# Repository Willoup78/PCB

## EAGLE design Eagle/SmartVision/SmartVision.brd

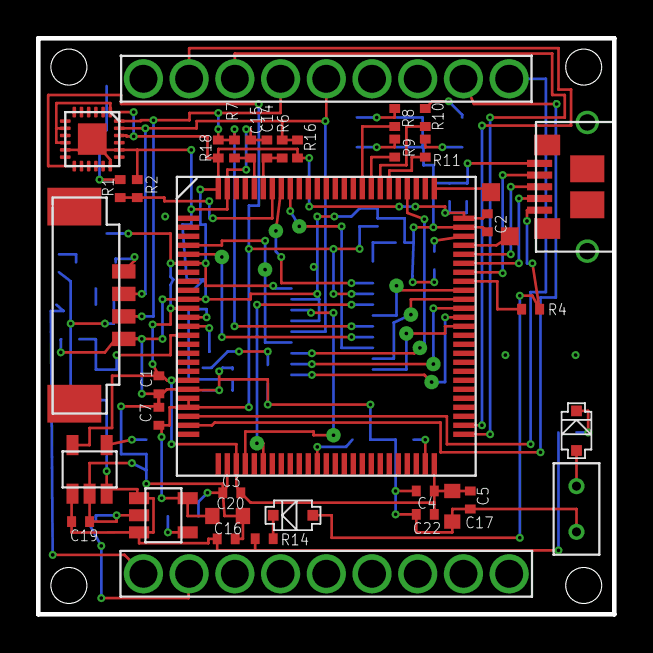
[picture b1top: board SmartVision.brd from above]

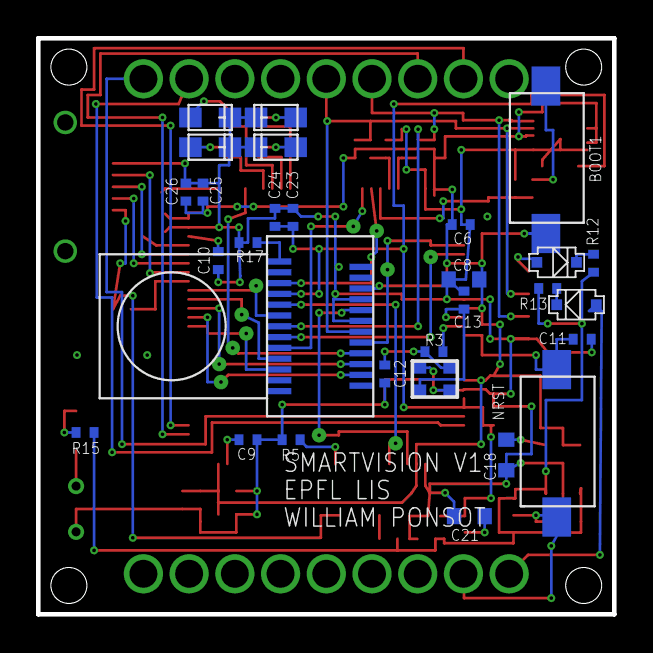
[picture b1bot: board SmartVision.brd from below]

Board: 2 copper layers, 32.0 x 32.0 mm, 66 parts (29 on the bottom side), 58 nets.

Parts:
C1, C2, C3, C4, C5, C6, C7, C11, C22, C23, C24, C25, C26: 100nF; SMALL_MAVRIC_SMALL_MAVRIC_CAPACITOR_C0402
C8: 10uF, 10V; SMALL_MAVRIC_SMALL_MAVRIC_CAPACITOR_C0603
C9, C10: 2.2uF; SMALL_MAVRIC_SMALL_MAVRIC_CAPACITOR_C0402
C12, C13: 12pF; SMALL_MAVRIC_SMALL_MAVRIC_CAPACITOR_C0402
C14, C15: 22pF; SMALL_MAVRIC_SMALL_MAVRIC_CAPACITOR_C0402
C16, C19: 1uF; SMALL_MAVRIC_SMALL_MAVRIC_CAPACITOR_C0402
C17, C18, C20, C21: 4.7uF; SMALL_MAVRIC_SMALL_MAVRIC_CAPACITOR_C0603
R1, R2, R5: 1K; SMALL_MAVRIC_SMALL_MAVRIC_RESISTOR_R0402
R3, R8, R9, R10, R11: 402; SMALL_MAVRIC_SMALL_MAVRIC_RESISTOR_R0402
R4, R6, R7, R16, R18: 4.7K; SMALL_MAVRIC_SMALL_MAVRIC_RESISTOR_R0402
R12, R13: 28; SMALL_MAVRIC_SMALL_MAVRIC_RESISTOR_R0402
R14, R15: 12.5; SMALL_MAVRIC_SMALL_MAVRIC_RESISTOR_R0402
R17: 10K; SMALL_MAVRIC_SMALL_MAVRIC_RESISTOR_R0402
U1: SMALL_MAVRIC_IMU_MPU-9250; SMALL_MAVRIC_SMALL_MAVRIC_QFN-24_3.0X3.0MM
U$1: STM32F407VGT6-100
U$2, U$7: VOLTAGE_REGULATOR_3V
U$4: MICRO_USB_PLUG
U$11: CON_CAMERA_FPC_25P_0.3MM
U$29, U$31: SWITCH_OFF_(ON)
U$40, U$41, U$42, U$43: LED
U$52: CON_2.54MM_18PINS_STACKABLE
U$53: CON_1.25MM_4PINS
U$54, U$55, U$57, U$61: DIODE_SCHOTTKY
U$59: CON_2.54MM_2PINS
U$63, U$64: PAD_FLASH
Y1: SMALL_MAVRIC_ABM10; SMALL_MAVRIC_OSCILLATOR_ABM10

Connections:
CAN2_RX: U$1.P51, U$52.P16
CAN2_TX: U$1.P52, U$52.P17
D0: U$1.P63, U$11.P23
D1: U$1.P64, U$11.P2
D2: U$1.P65, U$11.P3
D3: U$1.P66, U$11.P22
D4: U$1.P79, U$11.P4
D5: U$1.P92, U$11.P21
D6: U$1.P4, U$11.P5
D7: U$1.P5, U$11.P20
GND: C1.2, C2.2, C3.2, C4.2, C5.2, C6.2, C7.2, C8.2, C9.2, C10.2, C11.1, C12.2, C13.2, C14.2, C15.2, C16.2, C17.1, C18.2, C19.2, C20.1, C21.2, C22.2, C23.2, C24.2, C25.2, C26.2, R2.1, R5.2, R17.1, U1.11, U1.18, U1.20, U1.CENTRAL_PAD, U$1.P10, U$1.P20, U$1.P27, U$1.P74, U$1.P99, U$2.P2, U$4.P5, U$7.P2, U$11.P7, U$11.P9, U$29.P$1, U$40.C, U$41.C, U$42.C, U$43.C, U$52.P2, U$53.P4, U$59.P2, Y1.2, Y1.4
HSYNC: U$1.P29, U$11.P8
I2C_SCL: R6.2, R16.1, U1.23, U$11.P6, U$52.P14, U$53.P2
I2C_SDA: R7.2, R18.1, U1.24, U$11.P19, U$52.P15, U$53.P3
unnamed: C21.1, U$7.P4
unnamed: C18.1, U$2.P4
unnamed: R17.2, U$11.P13
unnamed: R11.2, U$1.P81
unnamed: R10.2, U$1.P82
unnamed: R9.2, U$1.P83
unnamed: R8.2, U$1.P84
unnamed: C13.1, U$1.P12, Y1.3
unnamed: R8.1, U$40.A
unnamed: C12.1, R3.2, Y1.1
unnamed: R9.1, U$41.A
unnamed: R10.1, U$42.A
unnamed: R3.1, U$1.P13
unnamed: C15.1, R7.1, U$1.P96
unnamed: C9.1, U$1.P49
unnamed: C10.1, U$1.P73
unnamed: C14.1, R6.1, U$1.P95
unnamed: R4.1, U$1.P68
unnamed: C11.2, U$1.P14, U$29.P$2
unnamed: R1.1, U$31.P$2
unnamed: R1.2, R2.2, U$1.P94
unnamed: R5.1, U$1.P37
unnamed: R11.1, U$43.A
unnamed: R13.1, U$61.P2
unnamed: R15.1, U$54.P2
unnamed: R12.1, U$55.P2
unnamed: R14.1, U$57.P2
PCLK: U$1.P31, U$11.P17
SWCLK: U$1.P76, U$63.P$1
SWDIO: U$1.P72, U$64.P$1
UART4_RX: U$1.P24, U$52.P11
UART4_TX: U$1.P23, U$52.P10
USB_D+: U$1.P71, U$4.P3
USB_D-: U$1.P70, U$4.P2
USB_ID: U$1.P69, U$4.P4
USB_VBUS: R4.2, U$4.P1, U$57.P1
VBAT: C16.1, C19.1, R12.2, R13.2, R14.2, R15.2, U$2.P1, U$2.P3, U$7.P1, U$7.P3
VBAT_C: U$53.P1, U$55.P1
VBAT_P: U$54.P1, U$59.P1
VBAT_S: U$52.P1, U$61.P1
VCC: C1.1, C2.1, C3.1, C4.1, C5.1, C6.1, C8.1, C17.2, C22.1, C25.1, C26.1, R16.2, R18.2, U1.1, U1.8, U1.10, U1.22, U$1.P6, U$1.P11, U$1.P19, U$1.P28, U$1.P50, U$1.P75, U$1.P100, U$2.P5, U$11.P10, U$31.P$1
VCC_ANA: C7.1, C20.2, C23.1, C24.1, U1.13, U$1.P21, U$1.P22, U$7.P5, U$11.P16
VSYNC: U$1.P93, U$11.P15
XCLK: U$1.P67, U$11.P18

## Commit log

2016-05-06 PCB schematics done !
2016-05-09 Fix supply and boot problem
2016-05-09 Routing mostly complete !
2016-05-11 Routing finish
    Routing without autorouter.
    Need optimisation, symbol, value, …
2016-05-13 PCB ready for production
2016-05-13 PCB finish with BOM
2016-05-13 Add shopping configuration
